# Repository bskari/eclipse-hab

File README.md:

# eclipse-2017-hab
Code for the Solid State Depot high altitude balloon 2017 eclipse launch

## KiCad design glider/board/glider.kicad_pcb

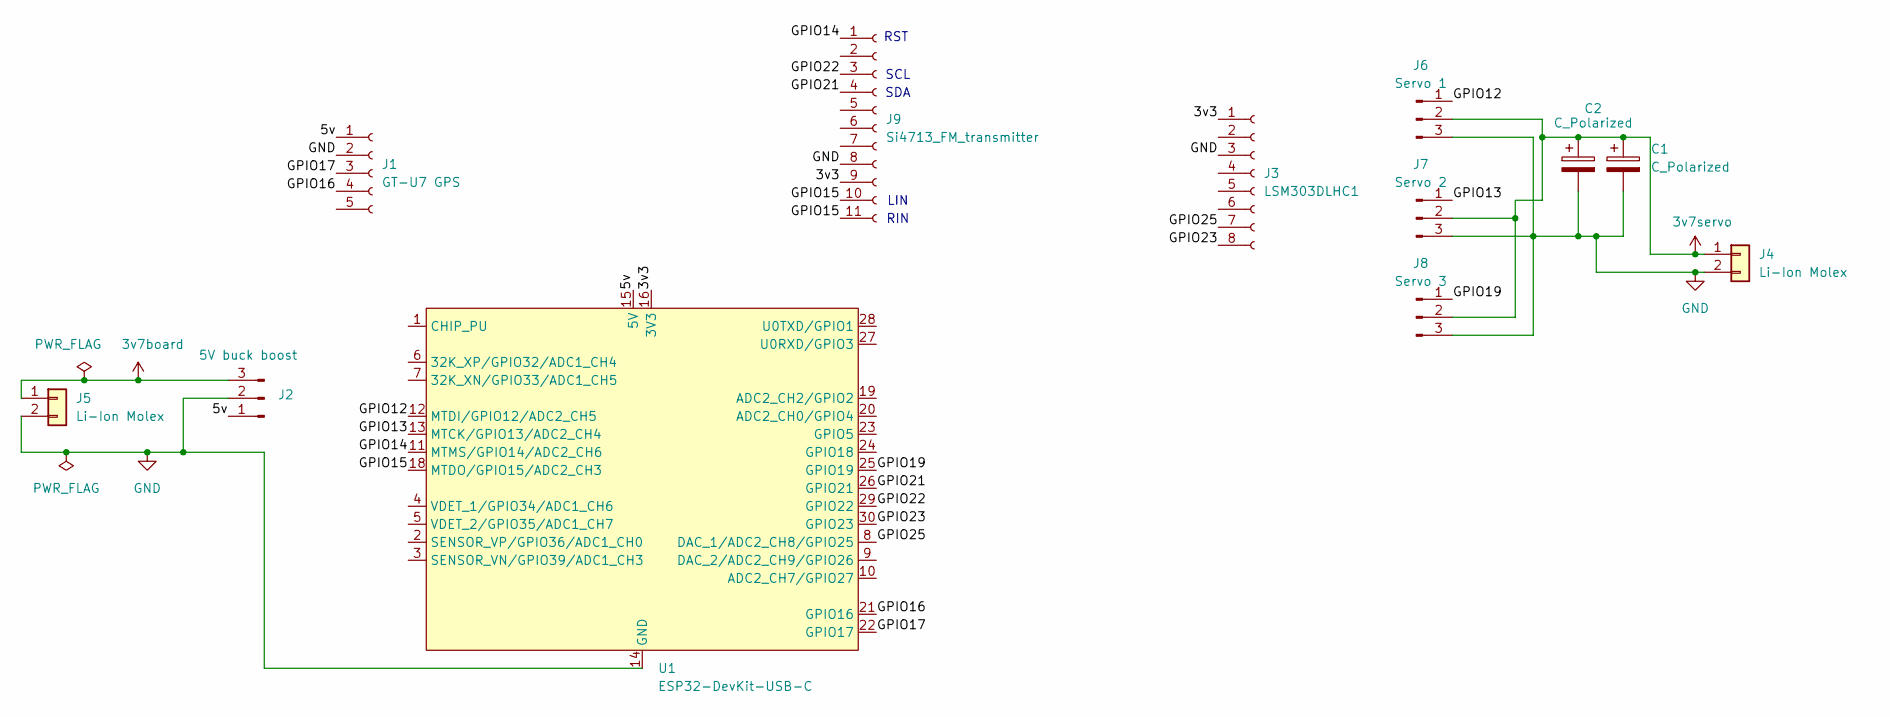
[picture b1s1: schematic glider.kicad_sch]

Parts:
C1, C2: C_Polarized; CP_Radial_D8.0mm_P3.50mm
J1: GT-U7 GPS; PinSocket_1x05_P2.54mm_Vertical
J2: 5V buck boost; PinHeader_1x03_P2.54mm_Vertical
J3: LSM303DLHC1; PinSocket_1x08_P2.54mm_Vertical
J4, J5: Li-Ion Molex; JST_PH_B2B-PH-K_1x02_P2.00mm_Vertical
J6: Servo 1; PinHeader_1x03_P2.54mm_Vertical
J7: Servo 2; PinHeader_1x03_P2.54mm_Vertical
J8: Servo 3; PinHeader_1x03_P2.54mm_Vertical
J9: Si4713_FM_transmitter; PinSocket_1x11_P2.54mm_Vertical
U1: ESP32-DevKit-USB-C

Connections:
3v7board: J2.3, J5.1
3v7servo: C1.1, C2.1, J4.1, J6.2, J7.2, J8.2
/3v3: J3.1, J9.9, U1.16 (3V3)
/5v: J1.1, J2.1, U1.15 (5V)
/GPIO12: J6.1, U1.12 (MTDI/GPIO12/ADC2_CH5)
/GPIO13: J7.1, U1.13 (MTCK/GPIO13/ADC2_CH4)
/GPIO14: J9.1, U1.11 (MTMS/GPIO14/ADC2_CH6)
/GPIO15: J9.10, J9.11, U1.18 (MTDO/GPIO15/ADC2_CH3)
/GPIO16: J1.4, U1.21 (GPIO16)
/GPIO17: J1.3, U1.22 (GPIO17)
/GPIO19: J8.1, U1.25 (GPIO19)
/GPIO21: J9.4, U1.26 (GPIO21)
/GPIO22: J9.3, U1.29 (GPIO22)
/GPIO23: J3.8, U1.30 (GPIO23)
/GPIO25: J3.7, U1.8 (DAC_1/ADC2_CH8/GPIO25)
GND: C1.2, C2.2, J1.2, J2.2, J3.3, J4.2, J5.2, J6.3, J7.3, J8.3, J9.8, U1.14 (GND), U1.17 (GND)

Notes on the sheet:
SCL
RST
SDA
LIN
RIN

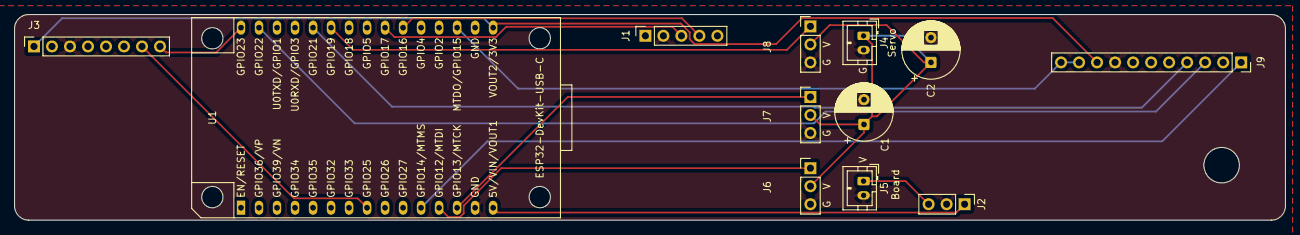
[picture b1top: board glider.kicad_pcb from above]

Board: 2 copper layers, 179.2 x 29.0 mm, 12 parts (0 on the bottom side), 16 nets.

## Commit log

2017-07-19 Add Python script to record video and time lapse
2017-07-19 Add script to setup virtualenv
2017-07-19 Add burn script
2017-07-19 Fix apt typo
2017-07-19 Fix unzip option
2017-07-19 Fix typos
2017-07-20 Print out some debug information
2017-07-20 Add script to log the CPU temperature
2017-07-21 Add RTL SDR stuff
2017-07-22 Log the temperature and shutdown when low on disk space
2017-07-22 Add setup script for SDR
2017-07-23 Print temperature too
2017-07-23 Change default temperature log rotation
2017-07-23 Add SSH banner
2017-07-23 Fix banner
2017-07-23 Use pv to monitor squelch ouput
2017-07-23 Exit cleanly if low disk space
2017-07-24 Assume yes on apt install
2017-07-24 Fix more install dependencies
2017-07-25 Always download the latest version of raspi-config
2017-07-25 Save the shutdown time
2017-07-25 Fix Python 3 problem
2017-07-25 Log times when checking disk space for debugging
2017-07-26 Add script to plot temperatures
2017-07-26 Log errors to disk
2017-07-26 Add LED blinking for indicating status
2017-07-26 Fix missing import
2017-07-26 Fix LED monitor, don't use pgrep
    pgrep ignores arguments, so e.g.
    python foo.py
    will return 1 for `pgrep foo.py`
2017-07-26 Fix inverse LED logic
2017-07-26 Make error blink more
2017-07-27 Fix loggers
2017-07-27 Fix logging
2017-07-27 Make sure the disk activity LED is disabled
2017-07-28 Check for low disk space from within Python
    I was checking for low disk space in a Bash script, and parsing the
    output of running `df`. I think this was taking a lot of time because I
    was starting a bunch of processes, and may have been causing the video
    to skip a little bit, so just check from in Python now between saving
    videos.
2017-07-28 Fix PyLint warnings
2017-07-28 Remove shutdown script from watchdog
2017-08-03 Add serial port dump
2017-08-03 Add option to set squelch
2017-08-04 Add setup for interfaces
2017-08-04 Add shutdown script
2017-08-04 Fix dump serial
2017-08-04 Wait before shutting down shortly after boot
2017-08-04 Even shutdown -k blocks SSH login attempts, so don't do that
2017-08-04 Don't cut off serial data with date stamps
2017-08-05 Shut off unneeded devices to reduce power
2017-08-05 Fix disabling HDMI
2017-08-05 Fix disabling HDMI again
2017-08-05 Always install virtualenv requirements
2017-08-06 Save the messages from the SUP800F over serial
    Reading from the SUP800F is a little complicated, because we need to
    switch it to binary mode instead of NMEA mode.
2017-08-06 Add script to plot SUP800F serial dump
2017-08-09 Add option to skip GUI
2017-08-09 Better detection of SUP800F module
2017-08-14 Enable SPI BCM 2708
2017-08-14 Prefer USB serial port over others
2017-09-02 Use JSON config for serial
2017-09-02 Exclude timestamps
2020-08-30 Squelch settings
2024-01-14 Remove 2017
2024-01-16 Fix directories
2024-01-16 Cutdown Arduino sketch
2024-01-17 Turn on low power mode after configuring
2024-01-17 Activate relay
2024-01-27 Set burn time in app
2024-02-07 Update to work with Direwolf
2024-02-24 Update RTL SDR monitors
2024-02-24 Add 7 segment display demo code
2024-02-25 Format sensor display
2024-02-25 Add TM1637 display local test
2024-02-25 Don't print leading zeroes on altitude below 10000
2024-02-25 Move to upper left
2024-02-25 Right justify temperature
2024-02-25 Add demo stuff to gitignore
2024-02-26 Timing tweaks: show altitude longer, shorter labels
2024-02-26 Rename an enum value to be clearer
2024-02-27 Start curses monitor
2024-02-27 Use windows
2024-02-27 Add borders
2024-02-27 Better refreshing
2024-02-28 Parse Direwolf output
    So when you run Direwolf, it prints the received APRS messages to the
    terminal. I was hoping I could just parse stdout or stderr from the
    process, but it looks like Direwolf actually uses something else to
    display these? So then I thought, I'll just have it log to a logfile and
    then tail that file. And that sort of worked, except we don't get the
    original APRS message, just a parsed version. So I had to work around
2024-02-28 Trying to get zombie processes to go away, still not working
2024-02-29 Fix terminating subprocesses
    You need to call communicate() after termination to avoid zombie
    processes
2024-02-29 Show distance from launch, and more units
2024-02-29 SHow recent station information
2024-02-29 Use Python logging
2024-02-29 Add argument parsing
2024-02-29 Add command line options
2024-03-01 Add colored error messages and clock
2024-03-01 Remove unused script
2024-03-01 Only update part of status
2024-03-01 Fix channel hopping
2024-03-02 Go back to using aprslib to parse
2024-03-03 Add APRS only option
2024-03-03 Add real messages to test mode
2024-03-03 Add APRS Unicode symbols
2024-03-03 Rename Python script
2024-03-03 Add script to aprslib parse single message
2024-03-03 More README
2024-03-03 Log when payload is dropping
2024-03-03 Reduce flickering
2024-03-03 Add janky Google Earth integration
2024-03-03 Drop server
2024-03-03 Switch back to APRS after hering RS41 message
2024-03-10 Simplify window management; save and load previous messages
2024-03-10 Add warning to parse_one
2024-03-10 Remove pv
2024-03-18 Don't load previuos when in test mode
2024-03-18 Don't save messages in test mode
2024-03-18 Add comments
2024-03-18 More comments
2024-03-24 Add button commands
2024-03-24 Update LoRa Makefile
2024-04-01 Refresh less to reduce flickering
2024-04-02 Add missing import
2024-04-03 Add constant, change log file
2024-04-03 Add simple LoRa Pi monitor
2024-04-03 Parse temperature
2024-04-03 Write LoRa KML file
2024-04-03 Only log movements to KML
2024-04-03 Add rsync script to download images
2024-04-04 First commit of logger
2024-04-05 Logger reads from sensors
2024-04-06 Do some sprintfs
2024-04-07 Fire cutdown after 2 hours if we haven't been configured
2024-04-07 Revert
2024-04-12 Add RS41 only option
2024-04-12 Add waypoints from 2024 eclipse mission
2024-11-11 Initial commit of glider
2024-11-12 MOre test stuff
2024-11-12 Add GPS breakout
2024-11-13 Fix GPS failing after ~10 minutes
2024-11-16 Move position into classes
2024-11-16 Correct for rotated LSM303
2024-11-23 Elevator servo
2024-11-25 Add KiCad board
2024-11-25 Add workspace
2025-11-16 Add scripts to tail and display autorx
2026-01-03 Update board
2026-01-03 Gerber outputs for board
